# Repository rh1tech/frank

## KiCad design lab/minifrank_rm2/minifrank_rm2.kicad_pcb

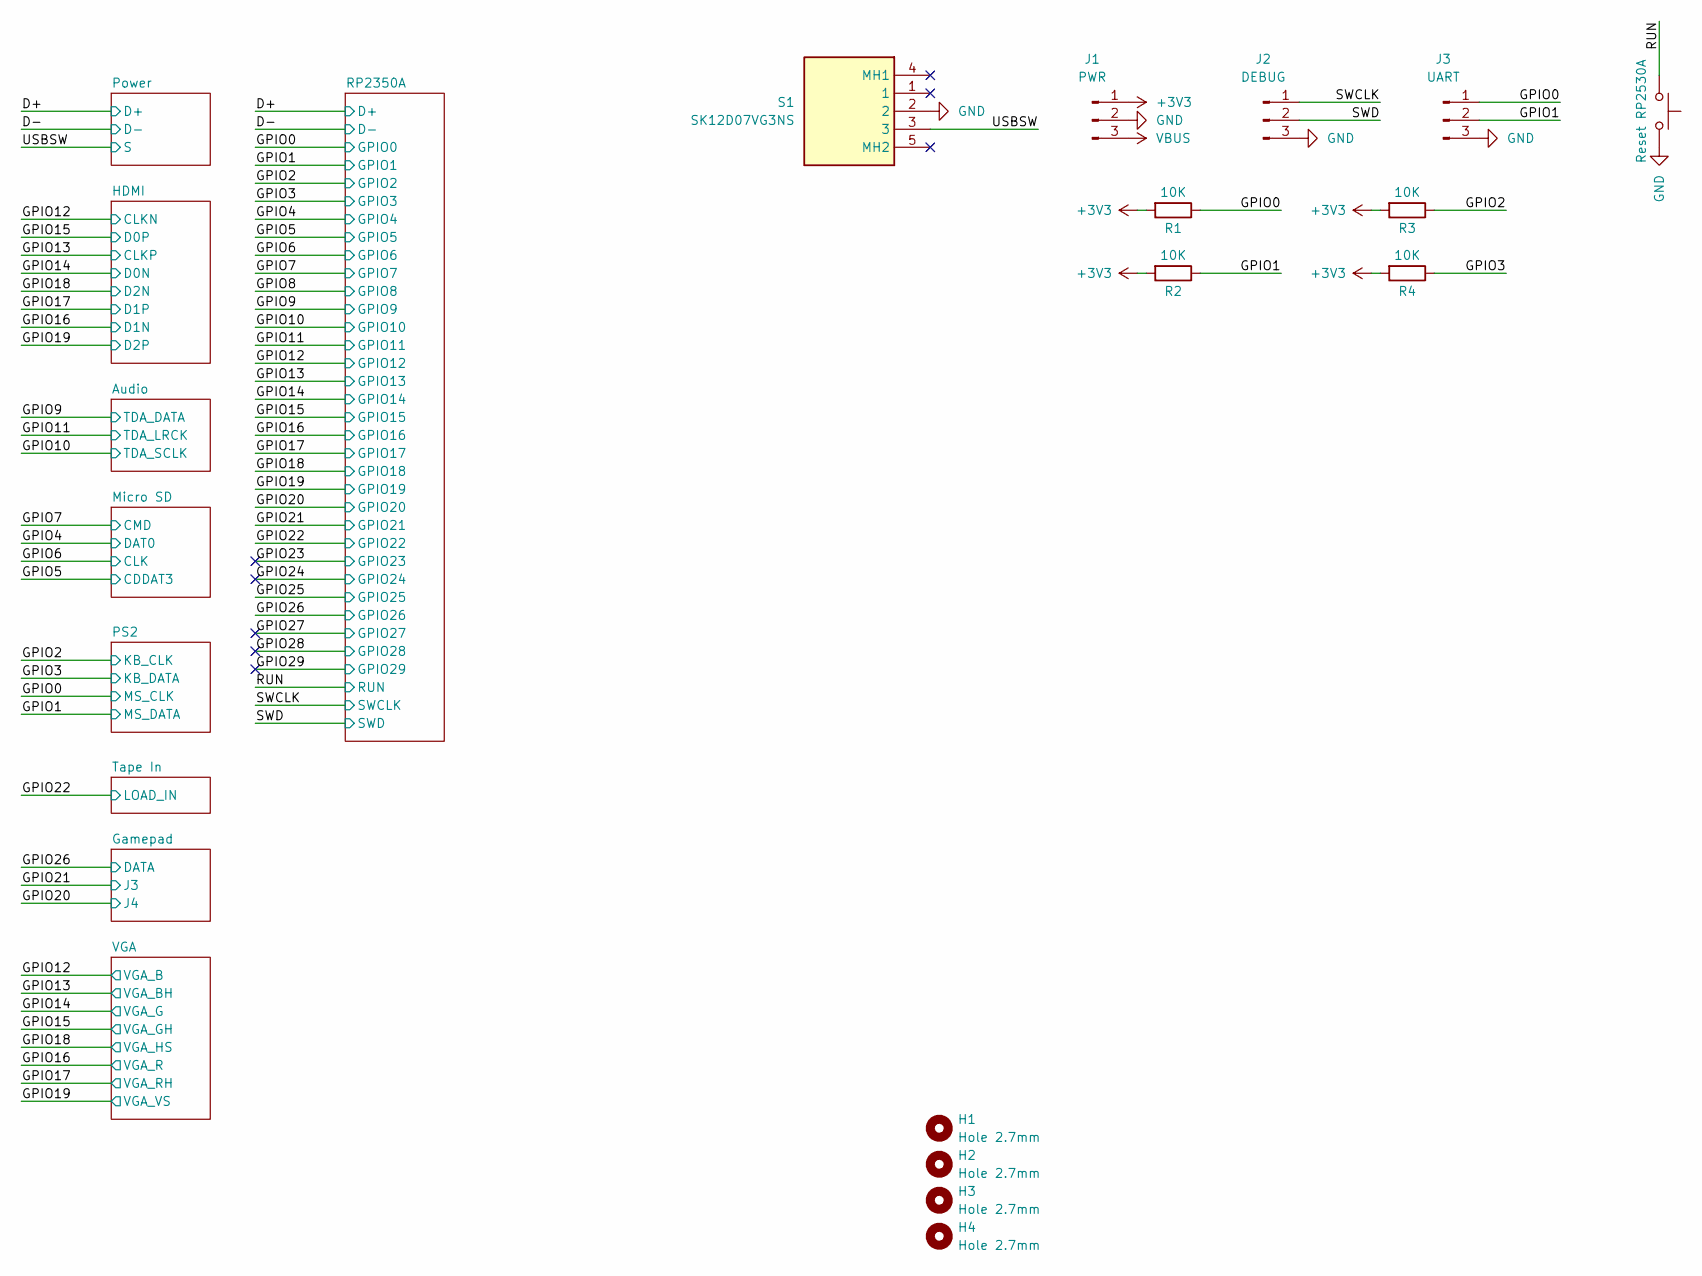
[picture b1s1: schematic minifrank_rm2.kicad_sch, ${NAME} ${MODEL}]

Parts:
H1, H2, H3, H4: Hole 2.7mm; Mounting Hole (2.7mm)
J1: PWR; Pin Header (1x03)
J2: DEBUG; Pin Header (1x03)
J3: UART; Pin Header (1x03)
R1, R2, R3, R4: 10K; R_0603_1608Metric
S1: SK12D07VG3NS; Mouser Part Number 611-SK12D07VG3NS
S2: Reset RP2530A; TACT-SIDE-4623

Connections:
+3V3: J1.1, R1.2, R2.2, R3.2, R4.2; also elsewhere on the board
/GPIO0: J3.1, R1.1; also elsewhere on the board
/GPIO1: J3.2, R2.1; also elsewhere on the board
/GPIO2: R3.1; also elsewhere on the board
/GPIO3: R4.1; also elsewhere on the board
/RUN: S2.1; also elsewhere on the board
/SWCLK: J2.1; also elsewhere on the board
/SWD: J2.2; also elsewhere on the board
/USBSW: S1.3; also elsewhere on the board
GND: J1.2, J2.3, J3.3, S1.2, S2.2; also elsewhere on the board
VBUS: J1.3; also elsewhere on the board

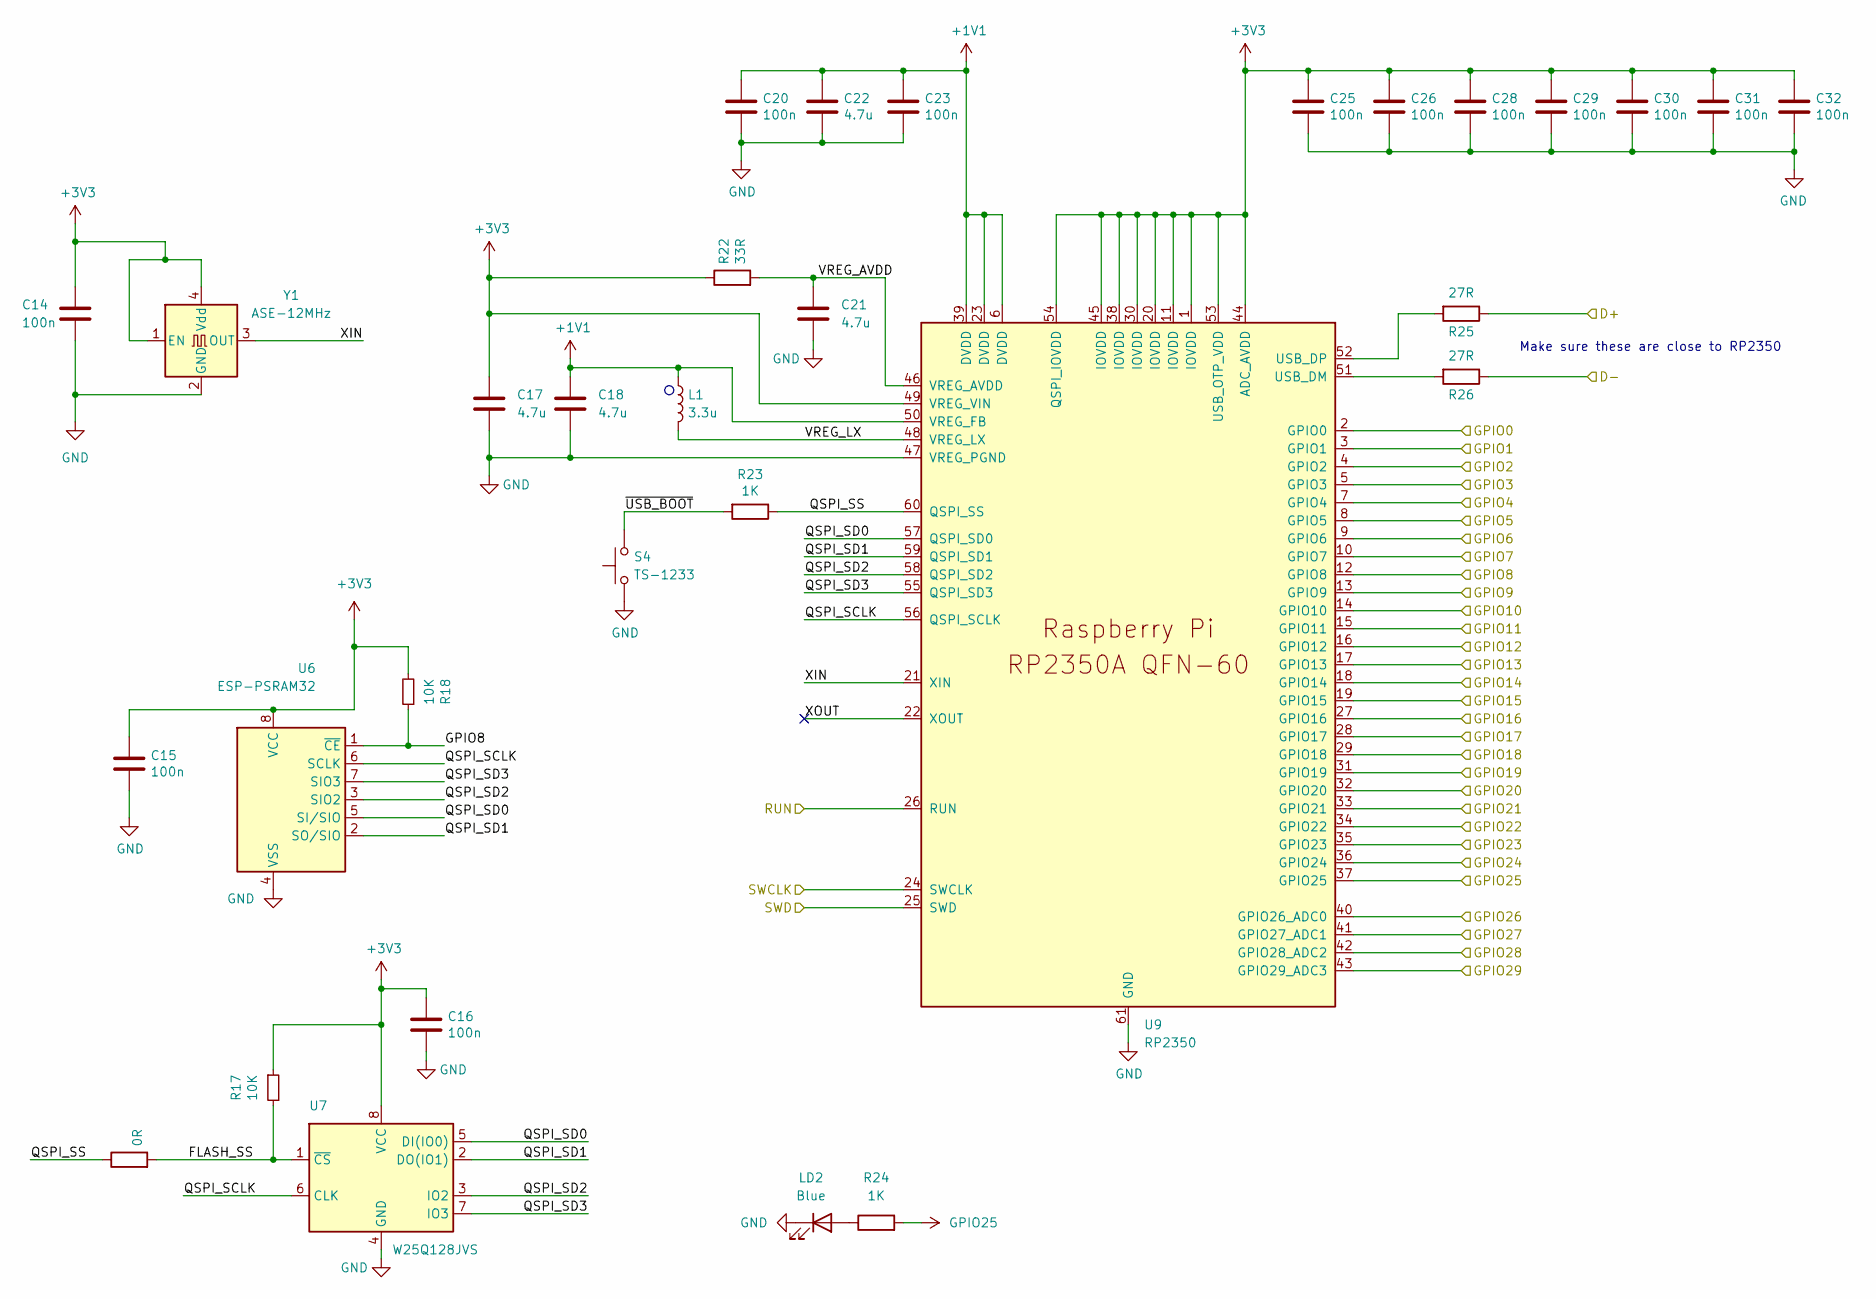
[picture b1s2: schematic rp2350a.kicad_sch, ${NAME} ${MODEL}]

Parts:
C14, C15, C16, C20, C23, C25, C26, C28, C29, C30, C31, C32: 100n; C_0603_1608Metric
C17, C18, C21, C22: 4.7u; C_0603_1608Metric
L1: 3.3u; L_pol_2016
LD2: Blue; LED_0603_1608Metric
R16: 0R; R_0603_1608Metric
R17, R18: 10K; R_0603_1608Metric
R22: 33R; R_0603_1608Metric
R23, R24: 1K; R_0603_1608Metric
R25, R26: 27R; R_0603_1608Metric
S4: TS-1233; TACT-SIDE-4623
U6: ESP-PSRAM32; SO-8
U7: W25Q128JVS; SOIC-8
U9: RP2350; QFN 60 (RP2350A)
Y1: ASE-12MHz; Oscillator_SMD_Abracon_ASE-4Pin_3.2x2.5mm

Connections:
+1V1: C18.1, C20.1, C22.1, C23.1, L1.1, U9.6 (DVDD), U9.23 (DVDD), U9.39 (DVDD), U9.50 (VREG_FB)
+3V3: C14.1, C15.1, C16.1, C17.1, C25.1, C26.1, C28.1, C29.1, C30.1, C31.1, C32.1, R17.1, R18.2, R22.1, U6.8 (VCC), U7.8 (VCC), U9.1 (IOVDD), U9.11 (IOVDD), U9.20 (IOVDD), U9.30 (IOVDD), U9.38 (IOVDD), U9.44 (ADC_AVDD), U9.45 (IOVDD), U9.49 (VREG_VIN), U9.53 (USB_OTP_VDD), U9.54 (QSPI_IOVDD), Y1.1 (EN), Y1.4 (Vdd); also elsewhere on the board
/D+: R25.1; also elsewhere on the board
/D-: R26.1; also elsewhere on the board
/GPIO0: U9.2 (GPIO0); also elsewhere on the board
/GPIO1: U9.3 (GPIO1); also elsewhere on the board
/GPIO2: U9.4 (GPIO2); also elsewhere on the board
/GPIO3: U9.5 (GPIO3); also elsewhere on the board
/GPIO4: U9.7 (GPIO4); also elsewhere on the board
/GPIO5: U9.8 (GPIO5); also elsewhere on the board
/GPIO6: U9.9 (GPIO6); also elsewhere on the board
/GPIO7: U9.10 (GPIO7); also elsewhere on the board
/GPIO8: R18.1, U6.1 (~CE), U9.12 (GPIO8)
/GPIO9: U9.13 (GPIO9); also elsewhere on the board
/GPIO10: U9.14 (GPIO10); also elsewhere on the board
/GPIO11: U9.15 (GPIO11); also elsewhere on the board
/GPIO12: U9.16 (GPIO12); also elsewhere on the board
/GPIO13: U9.17 (GPIO13); also elsewhere on the board
/GPIO14: U9.18 (GPIO14); also elsewhere on the board
/GPIO15: U9.19 (GPIO15); also elsewhere on the board
/GPIO16: U9.27 (GPIO16); also elsewhere on the board
/GPIO17: U9.28 (GPIO17); also elsewhere on the board
/GPIO18: U9.29 (GPIO18); also elsewhere on the board
/GPIO19: U9.31 (GPIO19); also elsewhere on the board
/GPIO20: U9.32 (GPIO20); also elsewhere on the board
/GPIO21: U9.33 (GPIO21); also elsewhere on the board
/GPIO22: U9.34 (GPIO22); also elsewhere on the board
/GPIO23: U9.35 (GPIO23)
/GPIO24: U9.36 (GPIO24)
/GPIO26: U9.40 (GPIO26_ADC0); also elsewhere on the board
/GPIO27: U9.41 (GPIO27_ADC1)
/GPIO28: U9.42 (GPIO28_ADC2)
/GPIO29: U9.43 (GPIO29_ADC3)
/RP2350A/FLASH_SS: R16.2, R17.2, U7.1 (~CS)
/RP2350A/QSPI_SCLK: U6.6 (SCLK), U7.6 (CLK), U9.56 (QSPI_SCLK)
/RP2350A/QSPI_SD0: U6.5 (SI/SIO), U7.5 (DI(IO0)), U9.57 (QSPI_SD0)
/RP2350A/QSPI_SD1: U6.2 (SO/SIO), U7.2 (DO(IO1)), U9.59 (QSPI_SD1)
/RP2350A/QSPI_SD2: U6.3 (SIO2), U7.3 (IO2), U9.58 (QSPI_SD2)
/RP2350A/QSPI_SD3: U6.7 (SIO3), U7.7 (IO3), U9.55 (QSPI_SD3)
/RP2350A/QSPI_SS: R16.1, R23.1, U9.60 (QSPI_SS)
/RP2350A/VREG_AVDD: C21.1, R22.2, U9.46 (VREG_AVDD)
/RP2350A/VREG_LX: L1.2, U9.48 (VREG_LX)
/RP2350A/XIN: U9.21 (XIN), Y1.3 (OUT)
/RP2350A/XOUT: U9.22 (XOUT)
/RP2350A/~USB_BOOT: R23.2, S4.2
/RUN: U9.26 (RUN); also elsewhere on the board
/SWCLK: U9.24 (SWCLK); also elsewhere on the board
/SWD: U9.25 (SWD); also elsewhere on the board
GND: C14.2, C15.2, C16.2, C17.2, C18.2, C20.2, C21.2, C22.2, C23.2, C25.2, C26.2, C28.2, C29.2, C30.2, C31.2, C32.2, LD2.1 (K), S4.1, U6.4 (VSS), U7.4 (GND), U9.47 (VREG_PGND), U9.61 (GND), Y1.2 (GND); also elsewhere on the board
GPIO25: R24.2, U9.37 (GPIO25)
unnamed: LD2.2 (A), R24.1
unnamed: R26.2, U9.51 (USB_DM)
unnamed: R25.2, U9.52 (USB_DP)

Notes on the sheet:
Make sure these are close to RP2350

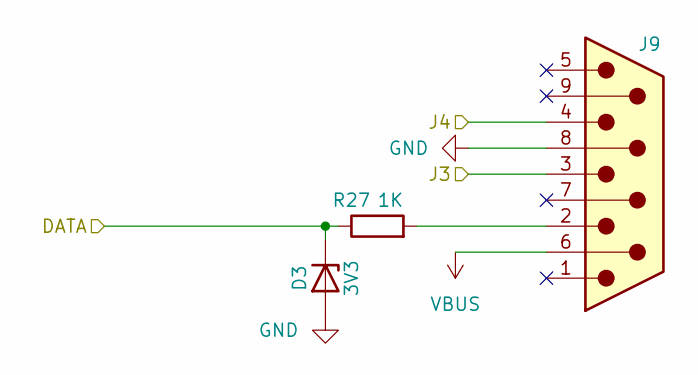
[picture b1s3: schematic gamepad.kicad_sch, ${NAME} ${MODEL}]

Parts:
D3: 3V3; Diode (SOD-323)
J9: GP2; D-SUB (9 pin, male, top mount)
R27: 1K; R_0603_1608Metric

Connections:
/GPIO20: J9.4; also elsewhere on the board
/GPIO21: J9.3; also elsewhere on the board
/GPIO26: D3.1 (K), R27.1; also elsewhere on the board
GND: D3.2 (A), J9.8; also elsewhere on the board
unnamed: J9.2, R27.2
VBUS: J9.6; also elsewhere on the board

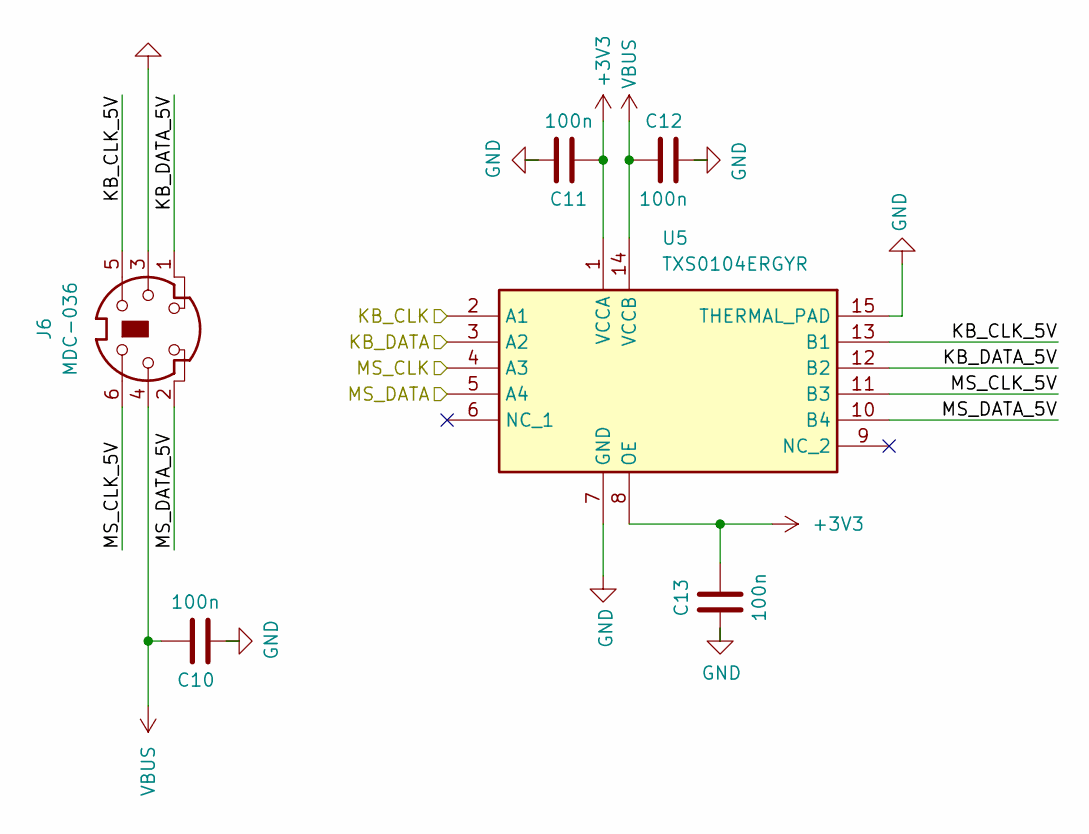
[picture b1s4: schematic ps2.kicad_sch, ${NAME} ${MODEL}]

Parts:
C10, C11, C12, C13: 100n; C_0603_1608Metric
J6: MDC-036; MiniDIN (6 Pin, female)
U5: TXS0104ERGYR; RGY_S-PVQFN-N14_; Mouser Part Number 595-TXS0104ERGYR

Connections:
+3V3: C11.1, C13.1, U5.1 (VCCA), U5.8 (OE); also elsewhere on the board
/GPIO0: U5.4 (A3); also elsewhere on the board
/GPIO1: U5.5 (A4); also elsewhere on the board
/GPIO2: U5.2 (A1); also elsewhere on the board
/GPIO3: U5.3 (A2); also elsewhere on the board
/PS2/KB_CLK_5V: J6.5, U5.13 (B1)
/PS2/KB_DATA_5V: J6.1, U5.12 (B2)
/PS2/MS_CLK_5V: J6.6, U5.11 (B3)
/PS2/MS_DATA_5V: J6.2, U5.10 (B4)
GND: C10.2, C11.2, C12.2, C13.2, J6.3, U5.7 (GND), U5.15 (THERMAL_PAD); also elsewhere on the board
VBUS: C10.1, C12.1, J6.4, U5.14 (VCCB); also elsewhere on the board

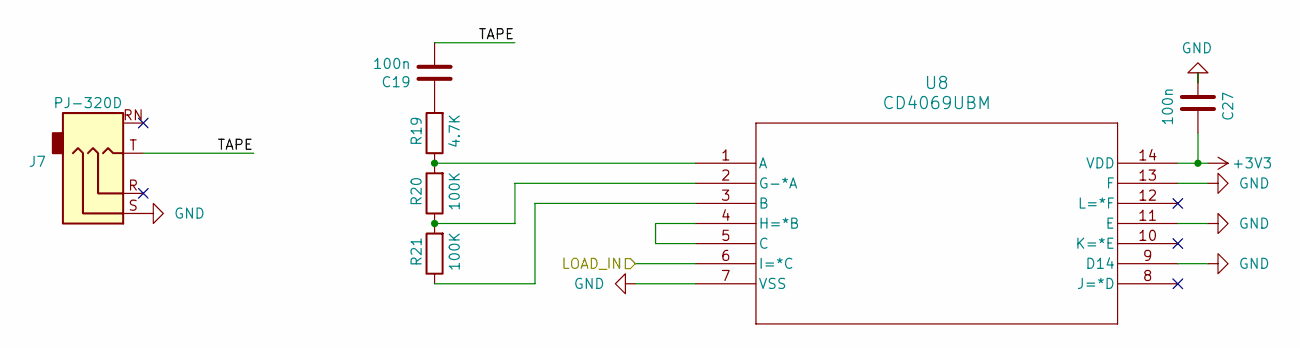
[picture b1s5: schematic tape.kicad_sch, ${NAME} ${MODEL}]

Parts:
C19, C27: 100n; C_0603_1608Metric
J7: PJ-320D; Jack (3.5mm, PJ-320D)
R19: 4.7K; R_0603_1608Metric
R20, R21: 100K; R_0603_1608Metric
U8: CD4069UBM; SOIC127P600X175-14N

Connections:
+3V3: C27.1, U8.14 (VDD); also elsewhere on the board
/GPIO22: U8.6 (I=*C); also elsewhere on the board
/Tape In/TAPE: C19.2, J7.T
GND: C27.2, J7.S, U8.7 (VSS), U8.9 (D14), U8.11 (E), U8.13 (F); also elsewhere on the board
unnamed: C19.1, R19.2
unnamed: R19.1, R20.2, U8.1 (A)
unnamed: R21.1, U8.3 (B)
unnamed: U8.4 (H=*B), U8.5 (C)
unnamed: R20.1, R21.2, U8.2 (G-*A)

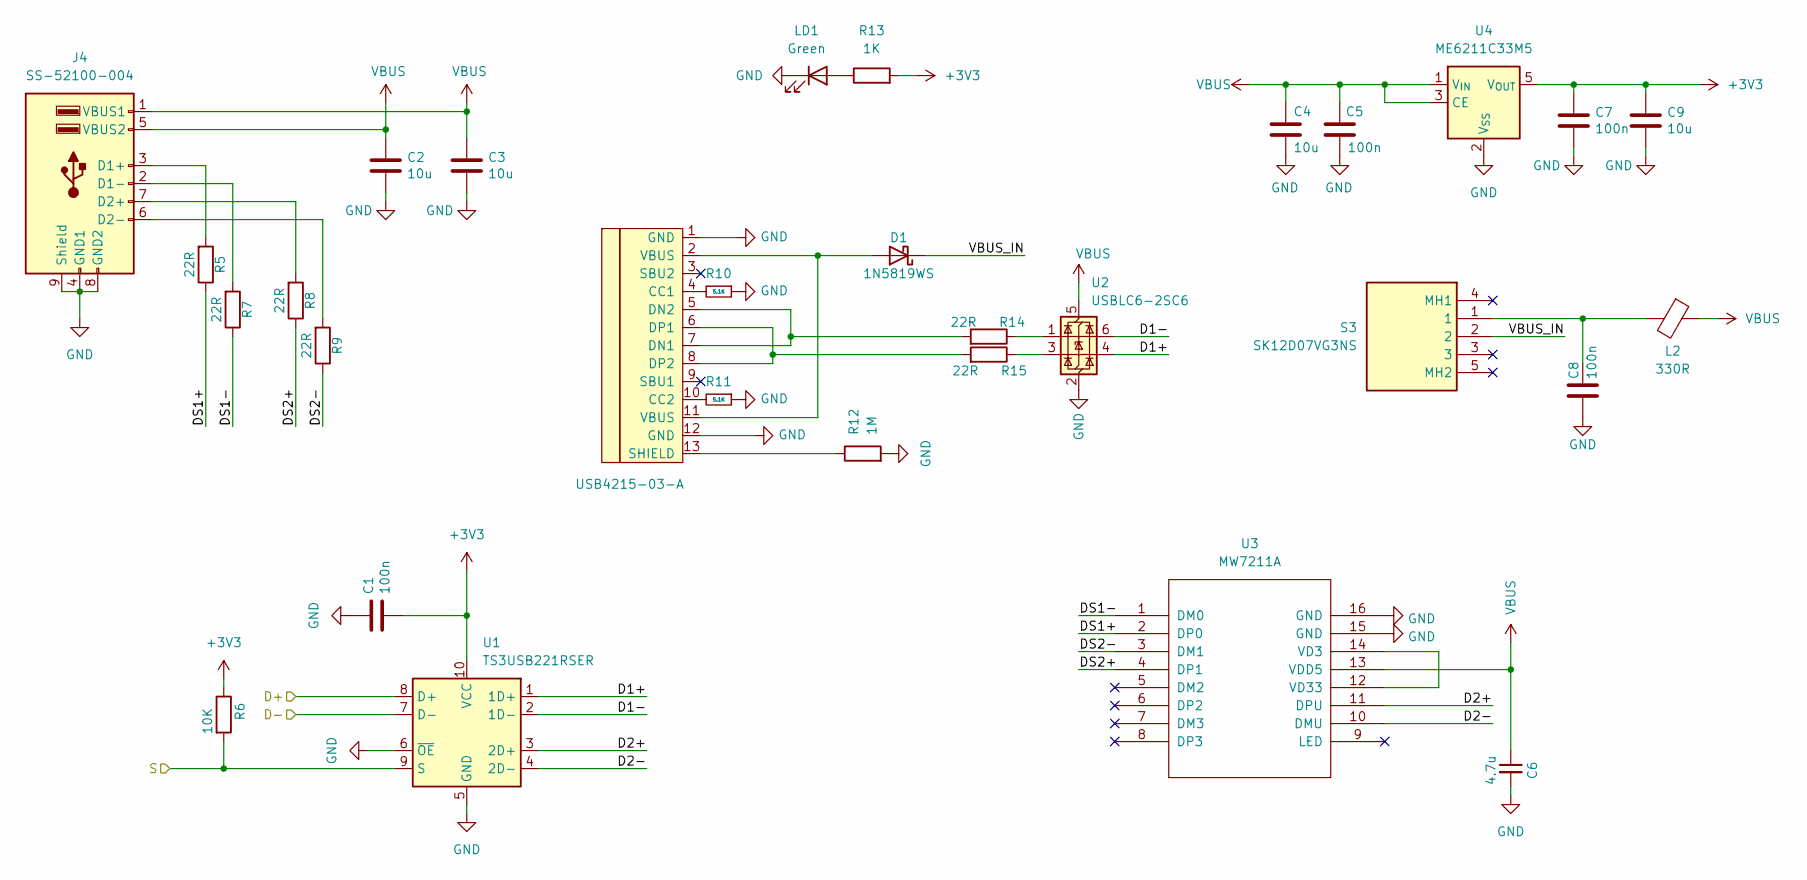
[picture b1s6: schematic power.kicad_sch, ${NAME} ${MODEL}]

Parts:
C1, C5, C8: 100n; C_0603_1608Metric
C2, C3, C4: 10u; C_0603_1608Metric
C6: 4.7u; C_0603_1608Metric; LCSC C1746
C7: 100n; C_0603_1608Metric; LCSC C1713
C9: 10u; C_0603_1608Metric; LCSC C1713
D1: 1N5819WS; Diode (SOD-323)
J4: SS-52100-004; USB Type A (stacked)
J5: USB4215-03-A; USB Type C; LCSC C165948
L2: 330R; L_0603_1608Metric
LD1: Green; LED_0603_1608Metric
R5, R7, R8, R9, R14, R15: 22R; R_0603_1608Metric
R6: 10K; R_0603_1608Metric
R10, R11: 5.1K; R_0603_1608Metric
R12: 1M; R_0603_1608Metric
R13: 1K; R_0603_1608Metric
S3: SK12D07VG3NS; Mouser Part Number 611-SK12D07VG3NS
U1: TS3USB221RSER; UQFN-10
U2: USBLC6-2SC6; SOT-23-6
U3: MW7211A; SOP-16
U4: ME6211C33M5; SOT-23-5

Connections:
+3V3: C1.2, C7.1, C9.1, R6.1, R13.2, U1.10 (VCC), U4.5 (V_{OUT}); also elsewhere on the board
/D+: U1.8 (D+); also elsewhere on the board
/D-: U1.7 (D-); also elsewhere on the board
/Power/D1+: U1.1 (1D+), U2.4 (I/O2)
/Power/D1-: U1.2 (1D-), U2.6 (I/O1)
/Power/D2+: U1.3 (2D+), U3.11 (DPU)
/Power/D2-: U1.4 (2D-), U3.10 (DMU)
/Power/DS1+: R5.1, U3.2 (DP0)
/Power/DS1-: R7.1, U3.1 (DM0)
/Power/DS2+: R8.1, U3.4 (DP1)
/Power/DS2-: R9.1, U3.3 (DM1)
/Power/VBUS_IN: D1.1 (K), S3.2
/USBSW: R6.2, U1.9 (S); also elsewhere on the board
GND: C1.1, C2.2, C3.2, C4.1, C5.1, C6.2, C7.2, C8.2, C9.2, J4.4 (GND1), J4.8 (GND2), J4.9 (Shield), J5.1 (GND), J5.12 (GND), LD1.1 (K), R10.1, R11.1, R12.2, U1.5 (GND), U1.6 (~OE), U2.2 (GND), U3.15 (GND), U3.16 (GND), U4.2 (V_{SS}); also elsewhere on the board
unnamed: C8.1, L2.2, S3.1
unnamed: D1.2 (A), J5.2 (VBUS), J5.11 (VBUS)
unnamed: J4.3 (D1+), R5.2
unnamed: J4.2 (D1-), R7.2
unnamed: J4.7 (D2+), R8.2
unnamed: J4.6 (D2-), R9.2
unnamed: J5.4 (CC1), R10.2
unnamed: J5.10 (CC2), R11.2
unnamed: J5.5 (DN2), J5.7 (DN1), R14.2
unnamed: J5.6 (DP1), J5.8 (DP2), R15.2
unnamed: J5.13 (SHIELD), R12.1
unnamed: LD1.2 (A), R13.1
unnamed: R14.1, U2.1 (I/O1)
unnamed: R15.1, U2.3 (I/O2)
unnamed: U3.12 (VD33), U3.14 (VD3)
VBUS: C2.1, C3.1, C4.2, C5.2, C6.1, J4.1 (VBUS1), J4.5 (VBUS2), L2.1, U2.5 (VBUS), U3.13 (VDD5), U4.1 (V_{IN}), U4.3 (CE); also elsewhere on the board

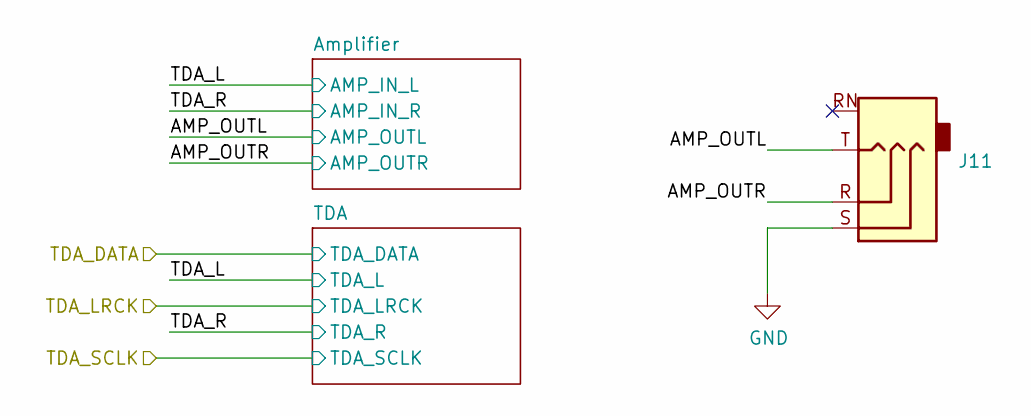
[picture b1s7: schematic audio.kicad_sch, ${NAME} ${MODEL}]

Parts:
J11: PJ-320D; Jack (3.5mm, PJ-320D)

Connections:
/Audio/AMP_OUTL: J11.T; also elsewhere on the board
/Audio/AMP_OUTR: J11.R; also elsewhere on the board
GND: J11.S; also elsewhere on the board

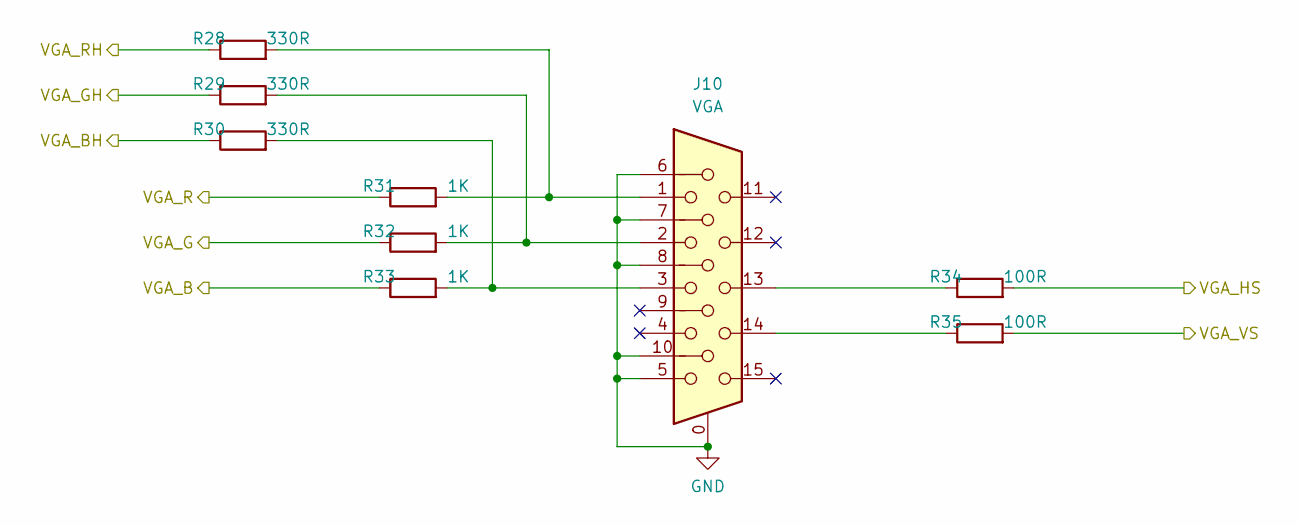
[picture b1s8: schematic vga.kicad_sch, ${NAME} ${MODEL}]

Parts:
J10: VGA; D-SUB (15 pin, female)
R28, R29, R30: 330R; R_0603_1608Metric
R31, R32, R33: 1K; R_0603_1608Metric
R34, R35: 100R; R_0603_1608Metric

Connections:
/GPIO12: R33.1; also elsewhere on the board
/GPIO13: R30.1; also elsewhere on the board
/GPIO14: R32.1; also elsewhere on the board
/GPIO15: R29.1; also elsewhere on the board
/GPIO16: R31.1; also elsewhere on the board
/GPIO17: R28.1; also elsewhere on the board
/GPIO18: R34.2; also elsewhere on the board
/GPIO19: R35.2; also elsewhere on the board
GND: J10.0, J10.5, J10.6, J10.7, J10.8, J10.10; also elsewhere on the board
unnamed: J10.1, R28.2, R31.2
unnamed: J10.2, R29.2, R32.2
unnamed: J10.3, R30.2, R33.2
unnamed: J10.13, R34.1
unnamed: J10.14, R35.1

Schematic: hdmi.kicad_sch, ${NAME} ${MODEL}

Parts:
C24: 100n; C_0603_1608Metric
D2: 1N5819WS; Diode (SOD-323)
J8: DC3RX19JA2; HDMI (female)
RN1, RN2: 270R; Resistor Array (4x0603)

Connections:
/GPIO12: RN1.4 (R4.1); also elsewhere on the board
/GPIO13: RN1.3 (R3.1); also elsewhere on the board
/GPIO14: RN1.2 (R2.1); also elsewhere on the board
/GPIO15: RN1.1 (R1.1); also elsewhere on the board
/GPIO16: RN2.4 (R4.1); also elsewhere on the board
/GPIO17: RN2.3 (R3.1); also elsewhere on the board
/GPIO18: RN2.2 (R2.1); also elsewhere on the board
/GPIO19: RN2.1 (R1.1); also elsewhere on the board
GND: C24.2, J8.2 (G_D2), J8.5 (G_D1), J8.8 (G_D0), J8.11 (G_CLK), J8.17 (G_DDC/CEC), J8.20 (SHIELD1), J8.21 (SHIELD2), J8.22 (SHIELD3), J8.23 (SHIELD4); also elsewhere on the board
unnamed: C24.1, D2.1 (K), J8.18 (+5V)
unnamed: J8.12 (CLKN), RN1.5 (R4.2)
unnamed: J8.10 (CLKP), RN1.6 (R3.2)
unnamed: J8.9 (D0N), RN1.7 (R2.2)
unnamed: J8.7 (D0P), RN1.8 (R1.2)
unnamed: J8.6 (D1N), RN2.5 (R4.2)
unnamed: J8.4 (D1P), RN2.6 (R3.2)
unnamed: J8.3 (D2N), RN2.7 (R2.2)
unnamed: J8.1 (D2P), RN2.8 (R1.2)
VBUS: D2.2 (A); also elsewhere on the board

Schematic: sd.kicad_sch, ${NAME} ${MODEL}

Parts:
C43: 100n; C_0603_1608Metric
J12: 104031-0811; MicroSD (SMD, long)

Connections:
+3V3: C43.2, J12.4 (VDD); also elsewhere on the board
/GPIO4: J12.7 (DAT0); also elsewhere on the board
/GPIO5: J12.2 (DAT3/CD); also elsewhere on the board
/GPIO6: J12.5 (CLK); also elsewhere on the board
/GPIO7: J12.3 (CMD); also elsewhere on the board
GND: C43.1, J12.6 (VSS); also elsewhere on the board

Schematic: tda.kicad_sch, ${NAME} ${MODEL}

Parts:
C33, C35: 10u; C_0603_1608Metric
C34: 100n; C_0603_1608Metric
R36: 100R; R_0603_1608Metric
R37, R38: 470R; R_0603_1608Metric
U10: TDA1387T; SO-8

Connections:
/Audio/TDA_L: R38.2, U10.6 (A_LEFT); also elsewhere on the board
/Audio/TDA_R: R37.1, U10.8 (A_RIGHT); also elsewhere on the board
/GPIO9: U10.3 (DATA); also elsewhere on the board
/GPIO10: U10.1 (SCLK); also elsewhere on the board
/GPIO11: U10.2 (LRCK); also elsewhere on the board
GND: C33.2, C34.2, C35.2, R37.2, R38.1, U10.4 (AGND); also elsewhere on the board
unnamed: C35.1, U10.7 (FLT)
unnamed: C33.1, C34.1, R36.1, U10.5 (VA)
VBUS: R36.2; also elsewhere on the board

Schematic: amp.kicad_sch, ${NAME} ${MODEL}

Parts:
C36, C37, C38, C40, C41: 10u; C_0603_1608Metric
C39: 10u; Capacitor (3528, tantalum, polar)
C42: 100n; C_0603_1608Metric
R39, R40, R41, R42, R43, R44: 10K; R_0603_1608Metric
R45, R46: 47K; R_0603_1608Metric
R47, R48: 20K; R_0603_1608Metric
R49: 100R; R_0603_1608Metric
U11: LM358; SO-8

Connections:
/Audio/AMP_OUTL: C40.2, R47.2; also elsewhere on the board
/Audio/AMP_OUTR: C41.2, R48.2; also elsewhere on the board
/Audio/TDA_L: C36.1, R39.1; also elsewhere on the board
/Audio/TDA_R: C37.1, R40.1; also elsewhere on the board
GND: C38.1, C39.1, C42.1, R39.2, R40.2, R42.1, R47.1, R48.1, U11.4 (V-); also elsewhere on the board
unnamed: C36.2, R43.2
unnamed: C37.2, R44.2
unnamed: C40.1, R45.1, U11.7
unnamed: C41.1, R46.1, U11.1
unnamed: C38.2, R41.1, R42.2, U11.3 (+), U11.5 (+)
unnamed: R44.1, R46.2, U11.2 (-)
unnamed: R43.1, R45.2, U11.6 (-)
unnamed: C39.2, C42.2, R41.2, R49.2, U11.8 (V+)
VBUS: R49.1; also elsewhere on the board

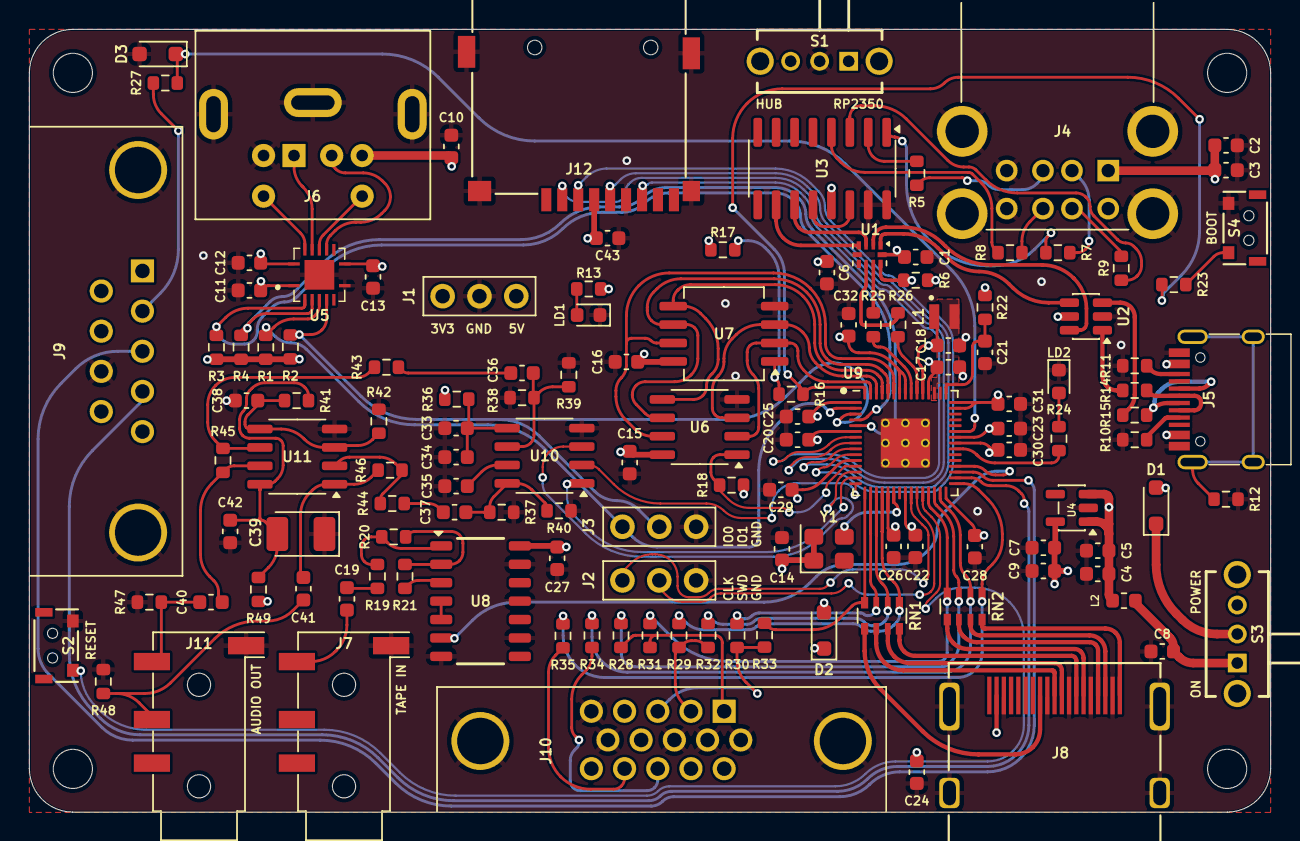
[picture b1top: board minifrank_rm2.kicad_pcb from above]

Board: 4 copper layers, 85.6 x 54.0 mm, 133 parts (0 on the bottom side), 112 nets.
